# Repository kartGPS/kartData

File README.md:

# kartData
Electrical Specifications and Software for the GPS puck intended for use in LETU Go-kart races. Designed initially by Caleb Schreier, Summer 2022

Hardware design is done. Software is in development.

This device supports WIFI, BlueTooth, and LoRa Radio Communications and is designed to be installed in Go-Karts for LeTourneau University's Official Go-Kart Race. 
The purpose of this device is to allow constant communication between the Kart and a stationary computer, potentially even many computers, as software is 
currently in development to allow the chip's microprocessor, an ESP32 WROVER, to connect to an external webserver and, through a websocket, convey process data 
to the server. The device is equipped with an accelerometer, GPS module, and in the case of insufficient WIFI, is equipped with a LoRa module, a low-power, radio-communications device with potential of data transmission at 10+ kilometers.

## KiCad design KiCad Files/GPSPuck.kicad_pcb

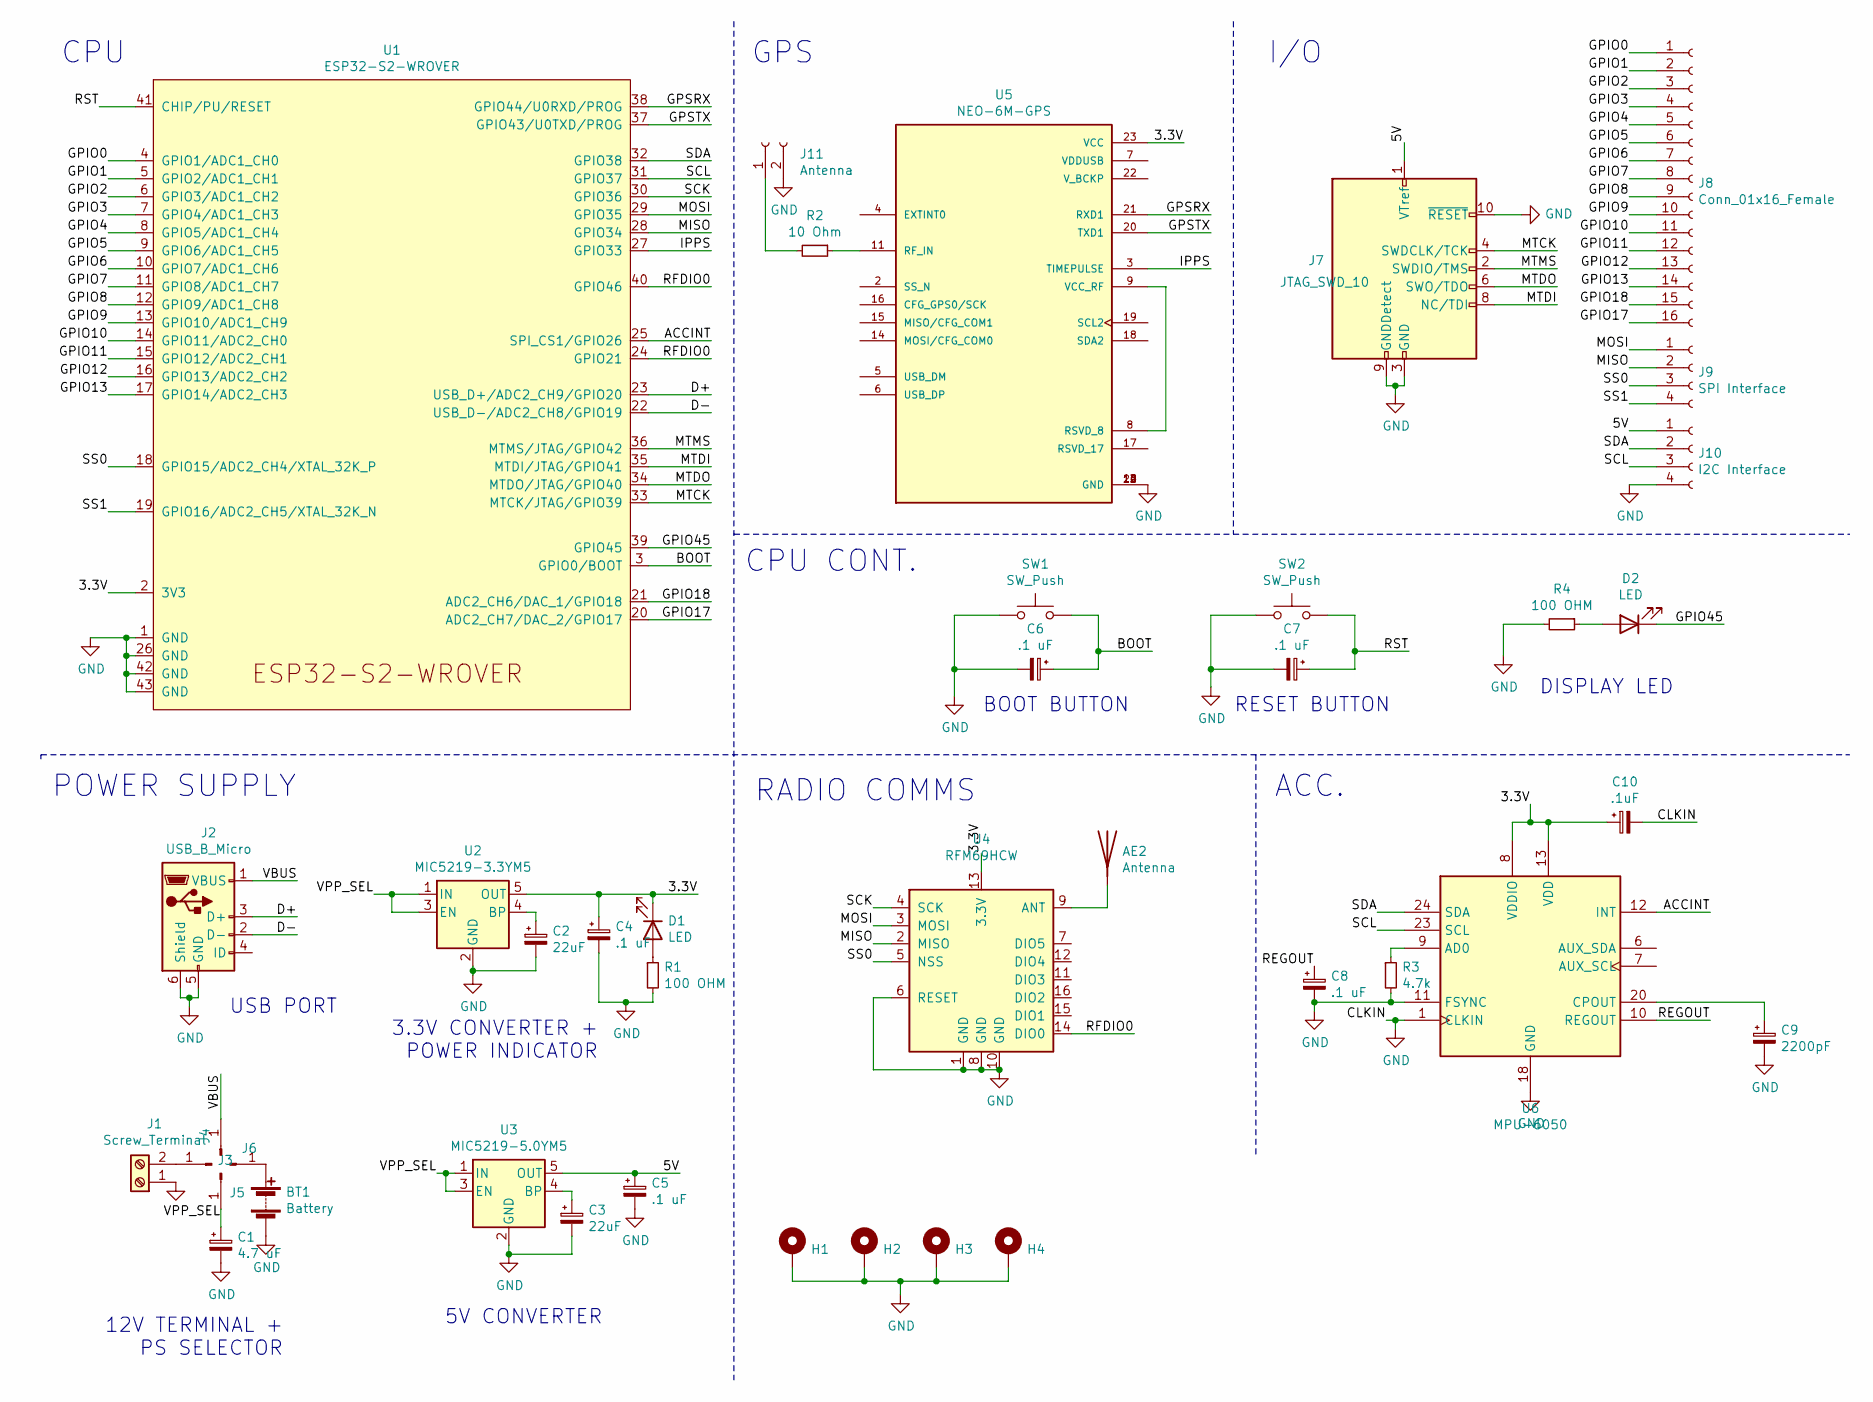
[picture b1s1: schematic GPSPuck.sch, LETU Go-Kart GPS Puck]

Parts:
AE2: Antenna; Texas_SWRA117D_2.4GHz_Left
BT1: Battery; BatteryHolder_Eagle_12BH611-GR
C1: 4.7 uF; CP_Elec_4x3
C2, C3: 22uF; CP_Elec_4x3
C4, C5, C6, C7, C8: .1 uF; CP_Elec_4x3
C9: 2200pF; C_0201_0603Metric_Pad0.64x0.40mm_HandSolder
C10: .1uF; CP_Elec_4x3
D1, D2: LED; LED_1206_3216Metric
H1, H2, H3, H4: MountingHole_Pad; MountingHole_3.2mm_M3_DIN965_Pad_TopBottom
J1: Screw_Terminal; TerminalBlock_Altech_AK300-2_P5.00mm
J2: USB_B_Micro; USB_Micro-B_Molex-105017-0001
J3: Conn_01x01; PinHeader_1x01_P2.54mm_Vertical
J4, J5, J6: Conn_01x01_Male; PinHeader_1x01_P2.54mm_Vertical
J7: JTAG_SWD_10; PinHeader_2x05_P2.54mm_Vertical
J8: Conn_01x16_Female; PinHeader_1x16_P2.54mm_Vertical
J9: SPI Interface; PinHeader_1x04_P2.54mm_Vertical
J10: I2C Interface; PinHeader_1x04_P2.54mm_Vertical
J11: Antenna; U.FL_Molex_MCRF_73412-0110_Vertical
R1, R4: 100 OHM; R_1206_3216Metric
R2: 10 Ohm; R_01005_0402Metric
R3: 4.7k; C_0805_2012Metric
SW1, SW2: SW_Push; SW_SPST_B3S-1000
U1: ESP32-S2-WROVER
U2: MIC5219-3.3YM5; SOT-23-5
U3: MIC5219-5.0YM5; SOT-23-5
U4: RFM69HCW; HOPERF_RFM9XW_SMD
U5: NEO-6M-GPS; ublox_NEO; PARTREV R15
U6: MPU-6050; InvenSense_QFN-24_4x4mm_P0.5mm

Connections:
/3.3V: C4.1, C10.1, D1.1 (K), U1.2 (3V3), U2.5 (OUT), U4.13 (3.3V), U5.23 (VCC), U6.8 (VDDIO), U6.13 (VDD)
/5V: C5.1, J7.1 (VTref), J10.1, U3.5 (OUT)
/ACCINT: U1.25 (SPI_CS1/GPIO26), U6.12 (INT)
/BOOT: C6.1, SW1.2, U1.3 (GPIO0/BOOT)
/D+: J2.3 (D+), U1.23 (USB_D+/ADC2_CH9/GPIO20)
/D-: J2.2 (D-), U1.22 (USB_D-/ADC2_CH8/GPIO19)
/GPIO0: J8.1, U1.4 (GPIO1/ADC1_CH0)
/GPIO1: J8.2, U1.5 (GPIO2/ADC1_CH1)
/GPIO2: J8.3, U1.6 (GPIO3/ADC1_CH2)
/GPIO3: J8.4, U1.7 (GPIO4/ADC1_CH3)
/GPIO4: J8.5, U1.8 (GPIO5/ADC1_CH4)
/GPIO5: J8.6, U1.9 (GPIO6/ADC1_CH5)
/GPIO6: J8.7, U1.10 (GPIO7/ADC1_CH6)
/GPIO7: J8.8, U1.11 (GPIO8/ADC1_CH7)
/GPIO8: J8.9, U1.12 (GPIO9/ADC1_CH8)
/GPIO9: J8.10, U1.13 (GPIO10/ADC1_CH9)
/GPIO10: J8.11, U1.14 (GPIO11/ADC2_CH0)
/GPIO11: J8.12, U1.15 (GPIO12/ADC2_CH1)
/GPIO12: J8.13, U1.16 (GPIO13/ADC2_CH2)
/GPIO13: J8.14, U1.17 (GPIO14/ADC2_CH3)
/GPIO17: J8.16, U1.20 (ADC2_CH7/DAC_2/GPIO17)
/GPIO18: J8.15, U1.21 (ADC2_CH6/DAC_1/GPIO18)
/GPIO45: D2.1 (K), U1.39 (GPIO45)
/GPSRX: U1.38 (GPIO44/U0RXD/PROG), U5.21 (RXD1)
/GPSTX: U1.37 (GPIO43/U0TXD/PROG), U5.20 (TXD1)
/IPPS: U1.27 (GPIO33), U5.3 (TIMEPULSE)
/MISO: J9.2, U1.28 (GPIO34), U4.2 (MISO)
/MOSI: J9.1, U1.29 (GPIO35), U4.3 (MOSI)
/MTCK: J7.4 (SWDCLK/TCK), U1.33 (MTCK/JTAG/GPIO39)
/MTDI: J7.8 (NC/TDI), U1.35 (MTDI/JTAG/GPIO41)
/MTDO: J7.6 (SWO/TDO), U1.34 (MTDO/JTAG/GPIO40)
/MTMS: J7.2 (SWDIO/TMS), U1.36 (MTMS/JTAG/GPIO42)
/REGOUT: C8.1, U6.10 (REGOUT)
/RFDIO0: U1.24 (GPIO21), U1.40 (GPIO46), U4.14 (DIO0)
/RST: C7.1, SW2.2, U1.41 (CHIP/PU/RESET)
/SCK: U1.30 (GPIO36), U4.4 (SCK)
/SCL: J10.3, U1.31 (GPIO37), U6.23 (SCL)
/SDA: J10.2, U1.32 (GPIO38), U6.24 (SDA)
/SS0: J9.3, U1.18 (GPIO15/ADC2_CH4/XTAL_32K_P), U4.5 (NSS)
/SS1: J9.4, U1.19 (GPIO16/ADC2_CH5/XTAL_32K_N)
/VBUS: J2.1 (VBUS), J4.1
/VPP_SEL: C1.1, J5.1, U2.1 (IN), U2.3 (EN), U3.1 (IN), U3.3 (EN)
GND: BT1.2 (-), C1.2, C2.2, C3.2, C4.2, C5.2, C6.2, C7.2, C8.2, C9.2, C10.2, H1.1, H2.1, H3.1, H4.1, J1.1, J2.5 (GND), J2.6 (Shield), J7.3 (GND), J7.5 (GND), J7.9 (GNDDetect), J7.10 (~RESET~), J10.4, J11.2, R1.2, R3.2, R4.2, SW1.1, SW2.1, U1.1 (GND), U1.26 (GND), U1.42 (GND), U1.43 (GND), U2.2 (GND), U3.2 (GND), U4.1 (GND), U4.6 (RESET), U4.8 (GND), U4.10 (GND), U5.10 (GND), U5.12 (GND), U5.13 (GND), U5.24 (GND), U6.1 (CLKIN), U6.11 (FSYNC), U6.18 (GND)
unnamed: AE2.1, U4.9 (ANT)
unnamed: BT1.1 (+), J6.1
unnamed: C2.1, U2.4 (BP)
unnamed: C3.1, U3.4 (BP)
unnamed: C9.1, U6.20 (CPOUT)
unnamed: D1.2 (A), R1.1
unnamed: D2.2 (A), R4.1
unnamed: J1.2, J3.1
unnamed: J11.1, R2.2
unnamed: R2.1, U5.11 (RF_IN)
unnamed: R3.1, U6.9 (AD0)
unnamed: U5.8 (RSVD_8), U5.9 (VCC_RF)

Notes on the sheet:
I/O
GPS
CPU
POWER SUPPLY
RADIO COMMS
ACC.
CPU CONT.
BOOT BUTTON
RESET BUTTON
DISPLAY LED
USB PORT
3.3V CONVERTER + POWER INDICATOR
5V CONVERTER
12V TERMINAL + PS SELECTOR

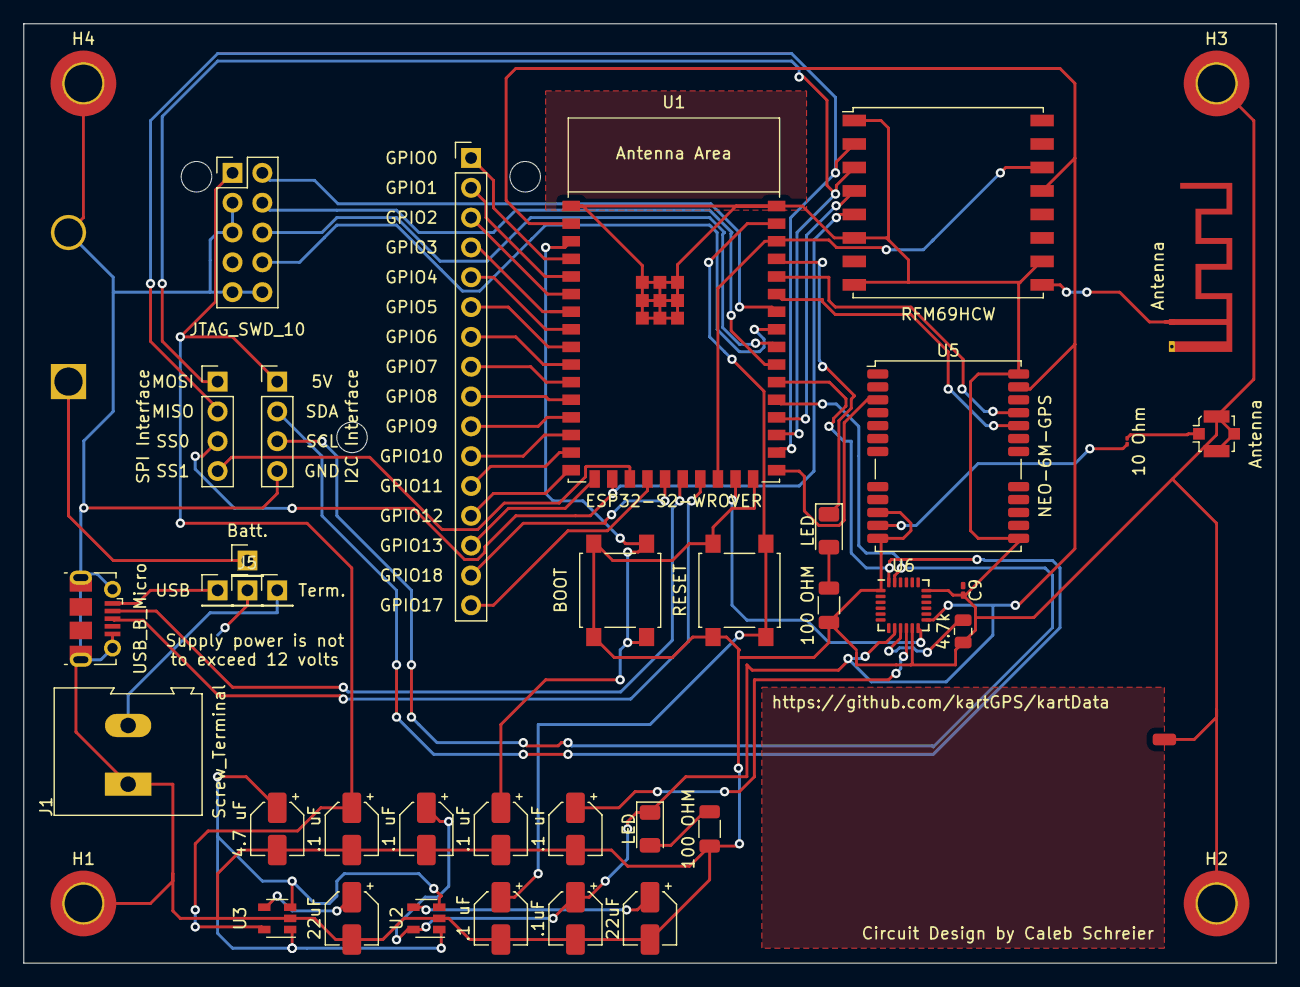
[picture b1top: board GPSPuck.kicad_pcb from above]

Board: 2 copper layers, 106.7 x 80.0 mm, 41 parts (1 on the bottom side), 55 nets.

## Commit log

2022-07-25 Initial KiCAD Project (unfinished layout, unrouted)
2022-07-26 Finished Layout and Routing
2022-07-28 Corrected antenna footprint, grounded hole masks, and added ground planes
2022-08-26 Create README.md
    Added Feature and some informal specifications to ReadMe
2022-08-26 Added Footprint Centroid file
2022-08-26 Fixed mislabeled C10
2022-08-26 Updated other changes in photos
2022-08-26 First Ed. -- JTAG Connector Differs from KiCad Specs
